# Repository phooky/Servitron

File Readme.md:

Servotron Six
=============

Servotron Six is a six-axis DC servo control board initially developed to support PUMA robot arms and their cousins. It presumes that each servo consists of a DC gearmotor, a quadrature encoder, and optionally an index channel. It uses a BeagleBone A5 or greater to control the system and is designed so that your application can run directly on the BeagleBone.

It has not yet been tested with the new BeagleBone Black.

Hardware
--------

The board is designed to run off a 24V power supply. A switching supply provides 5V to the logic chips and the BeagleBone. Each servo channel is driven by a VNH3SP30 which can provide a peak of ~20A.

The hardware design files are in the "electronics/six_axis_board" directory. The hardware is licenced under the CERN Open Hardware License v1.1.

Software
--------

The software which runs on the BeagleBone is in the "servotron" directory.

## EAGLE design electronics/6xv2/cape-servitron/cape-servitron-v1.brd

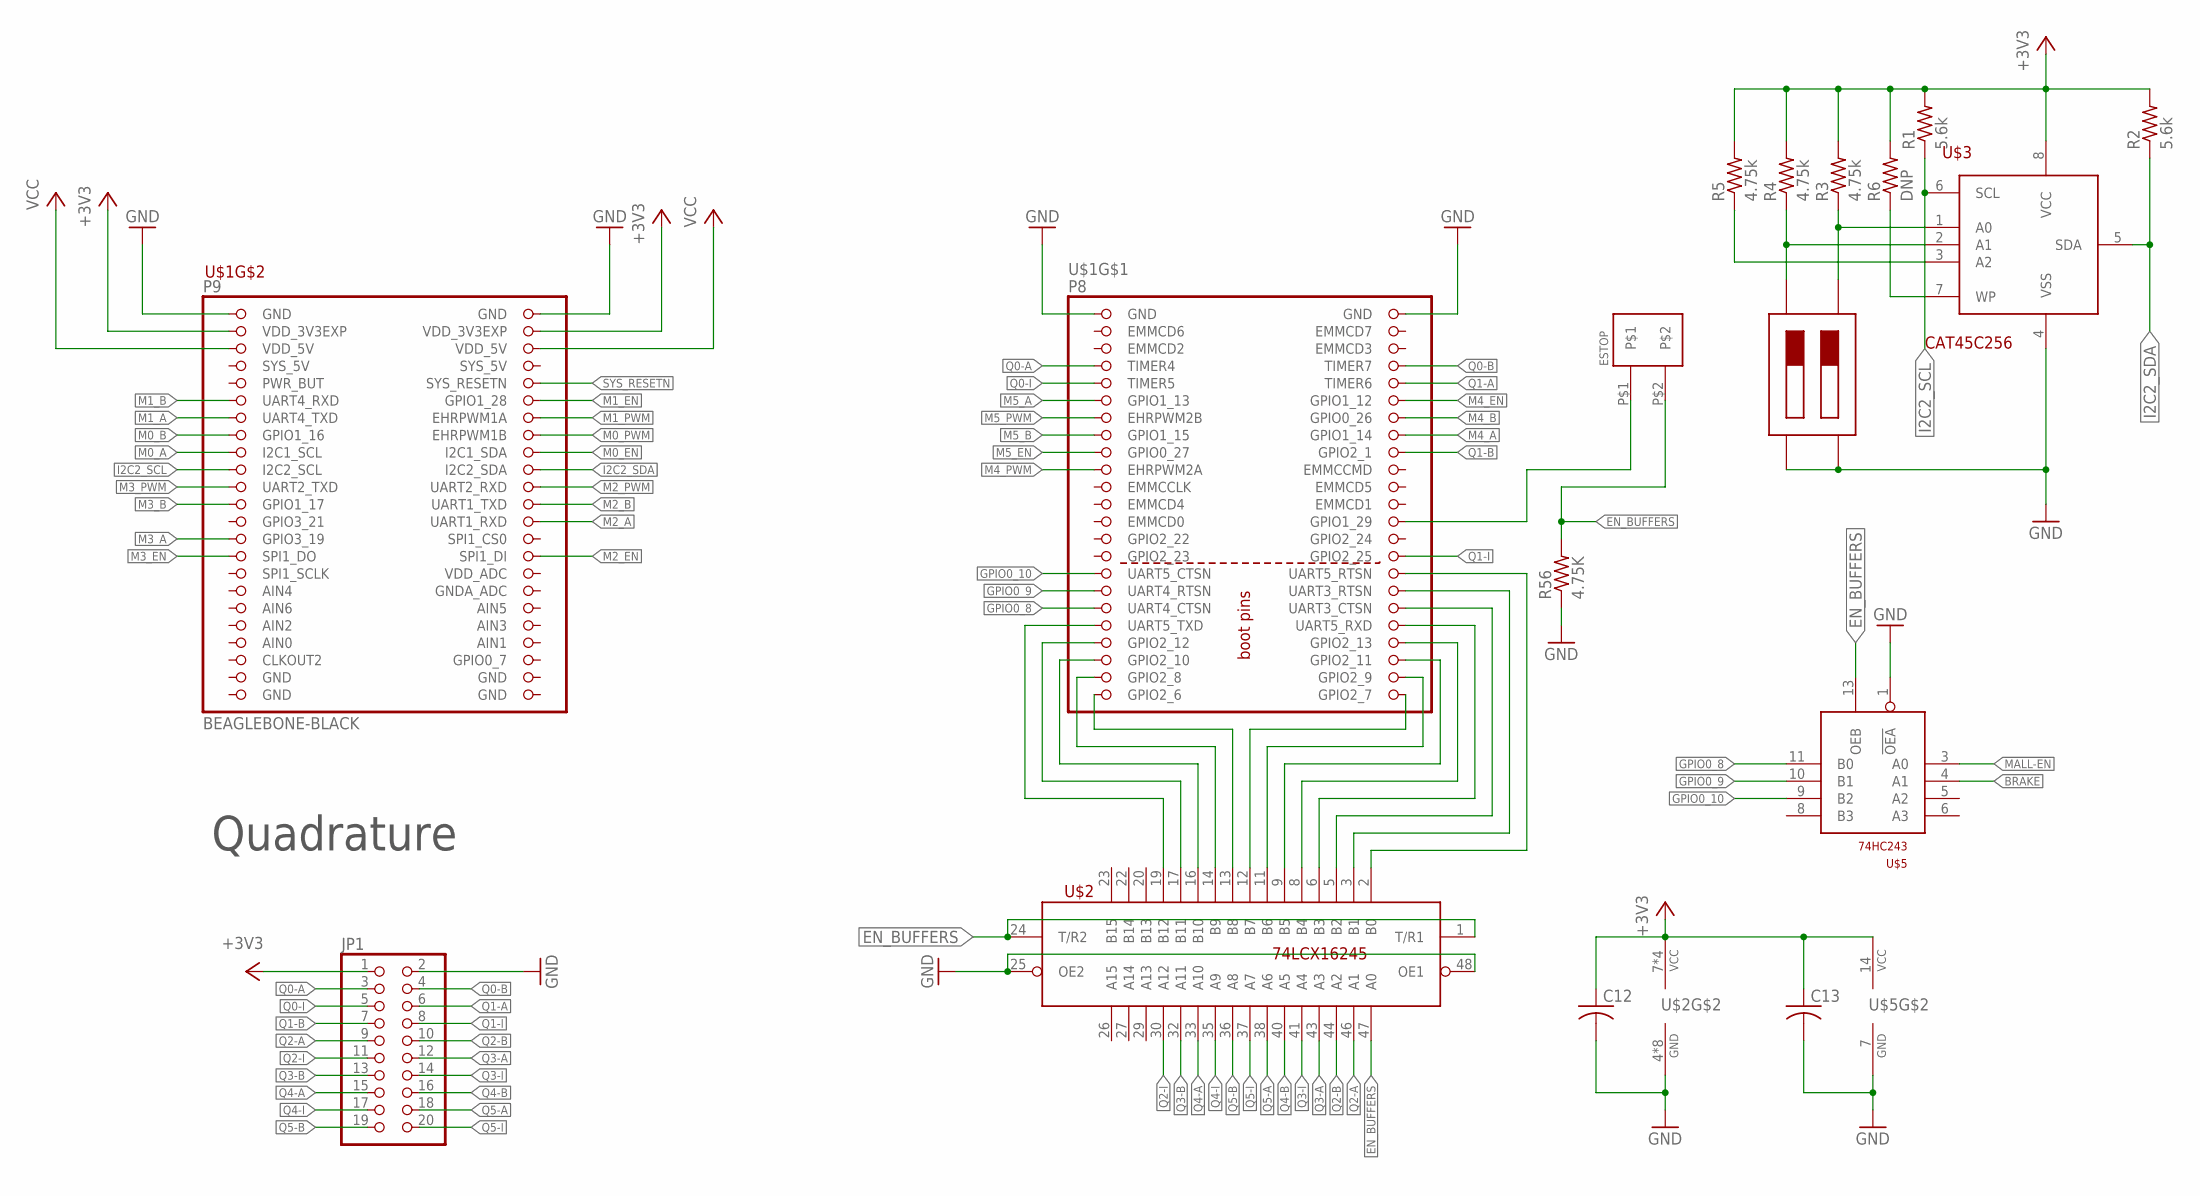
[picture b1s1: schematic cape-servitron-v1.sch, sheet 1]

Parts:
C12, C13: C-USC0805; C0805
ESTOP: PINHEAD-5MM-1X2; 5MM-HEADER-2
JP1: PINHD-2X10; 2X10
R1, R2: 5.6k; R0805
R3, R4, R5: 4.75k; R0805
R6: DNP; R0805
R56: 4.75K; R0805
U$1: BEAGLEBONE-BLACK; BEAGLEBONE_SHIELD
U$2: 74LCX16245; TSSOP-48
U$3: CAT24C2256Y; TSSOP-8
U$4: DIP-SW-2; CT219-2
U$5: 74HC243D; SO14

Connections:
!MALL-EN: U$5.3 (A0); also elsewhere on the board
+3V3: C12.1, C13.1, JP1.1, R1.2, R2.2, R3.2, R4.2, R5.2, R6.2, U$1.49 (VDD_3V3EXP), U$1.50 (VDD_3V3EXP), U$2.7 (VCC), U$2.18 (VCC), U$2.31 (VCC), U$2.42 (VCC), U$3.8 (VCC), U$5.14 (VCC); also elsewhere on the board
BRAKE: U$5.4 (A1); also elsewhere on the board
EN_BUFFERS: ESTOP.P$2, R56.2, U$2.1 (T/R1), U$2.24 (T/R2), U$2.47 (A0), U$5.13 (OEB)
GND: C12.2, C13.2, JP1.2, R56.1, U$1.1 (GND), U$1.2 (GND), U$1.47 (GND), U$1.48 (GND), U$1.89 (GND), U$1.90 (GND), U$1.91 (GND), U$1.92 (GND), U$2.4 (GND), U$2.10 (GND), U$2.15 (GND), U$2.21 (GND), U$2.25 (OE2), U$2.28 (GND), U$2.34 (GND), U$2.39 (GND), U$2.45 (GND), U$2.48 (OE1), U$3.4 (VSS), U$4.1, U$4.2, U$5.1 (!OEA), U$5.7 (GND); also elsewhere on the board
GPIO0_8: U$1.35 (UART4_CTSN), U$5.11 (B0)
GPIO0_9: U$1.33 (UART4_RTSN), U$5.10 (B1)
GPIO0_10: U$1.31 (UART5_CTSN), U$5.9 (B2)
I2C2_SCL: R1.1, U$1.65 (I2C2_SCL), U$3.6 (SCL)
I2C2_SDA: R2.1, U$1.66 (I2C2_SDA), U$3.5 (SDA)
M0_A: U$1.63 (I2C1_SCL); also elsewhere on the board
M0_B: U$1.61 (GPIO1_16); also elsewhere on the board
M0_EN: U$1.64 (I2C1_SDA); also elsewhere on the board
M0_PWM: U$1.62 (EHRPWM1B); also elsewhere on the board
M1_A: U$1.59 (UART4_TXD); also elsewhere on the board
M1_B: U$1.57 (UART4_RXD); also elsewhere on the board
M1_EN: U$1.58 (GPIO1_28); also elsewhere on the board
M1_PWM: U$1.60 (EHRPWM1A); also elsewhere on the board
M2_A: U$1.72 (UART1_RXD); also elsewhere on the board
M2_B: U$1.70 (UART1_TXD); also elsewhere on the board
M2_EN: U$1.76 (SPI1_DI); also elsewhere on the board
M2_PWM: U$1.68 (UART2_RXD); also elsewhere on the board
M3_A: U$1.73 (GPIO3_19); also elsewhere on the board
M3_B: U$1.69 (GPIO1_17); also elsewhere on the board
M3_EN: U$1.75 (SPI1_DO); also elsewhere on the board
M3_PWM: U$1.67 (UART2_TXD); also elsewhere on the board
M4_A: U$1.16 (GPIO1_14); also elsewhere on the board
M4_B: U$1.14 (GPIO0_26); also elsewhere on the board
M4_EN: U$1.12 (GPIO1_12); also elsewhere on the board
M4_PWM: U$1.19 (EHRPWM2A); also elsewhere on the board
M5_A: U$1.11 (GPIO1_13); also elsewhere on the board
M5_B: U$1.15 (GPIO1_15); also elsewhere on the board
M5_EN: U$1.17 (GPIO0_27); also elsewhere on the board
M5_PWM: U$1.13 (EHRPWM2B); also elsewhere on the board
unnamed: U$1.45 (GPIO2_6), U$2.13 (B8)
unnamed: U$1.46 (GPIO2_7), U$2.12 (B7)
unnamed: U$1.43 (GPIO2_8), U$2.14 (B9)
unnamed: U$1.44 (GPIO2_9), U$2.11 (B6)
unnamed: U$1.41 (GPIO2_10), U$2.16 (B10)
unnamed: U$1.42 (GPIO2_11), U$2.9 (B5)
unnamed: U$1.40 (GPIO2_13), U$2.8 (B4)
unnamed: U$1.39 (GPIO2_12), U$2.17 (B11)
unnamed: U$1.37 (UART5_TXD), U$2.19 (B12)
unnamed: U$1.38 (UART5_RXD), U$2.6 (B3)
unnamed: U$1.36 (UART3_CTSN), U$2.5 (B2)
unnamed: U$1.34 (UART3_RTSN), U$2.3 (B1)
unnamed: R3.1, U$3.1 (A0), U$4.4
unnamed: R4.1, U$3.2 (A1), U$4.3
unnamed: R5.1, U$3.3 (A2)
unnamed: R6.1, U$3.7 (WP)
unnamed: U$1.32 (UART5_RTSN), U$2.2 (B0)
unnamed: ESTOP.P$1, U$1.26 (GPIO1_29)
Q0-A: JP1.3, U$1.7 (TIMER4)
Q0-B: JP1.4, U$1.8 (TIMER7)
Q0-I: JP1.5, U$1.9 (TIMER5)
Q1-A: JP1.6, U$1.10 (TIMER6)
Q1-B: JP1.7, U$1.18 (GPIO2_1)
Q1-I: JP1.8, U$1.30 (GPIO2_25)
Q2-A: JP1.9, U$2.46 (A1)
Q2-B: JP1.10, U$2.44 (A2)
Q2-I: JP1.11, U$2.30 (A12)
Q3-A: JP1.12, U$2.43 (A3)
Q3-B: JP1.13, U$2.32 (A11)
Q3-I: JP1.14, U$2.41 (A4)
Q4-A: JP1.15, U$2.33 (A10)
Q4-B: JP1.16, U$2.40 (A5)
Q4-I: JP1.17, U$2.35 (A9)
Q5-A: JP1.18, U$2.38 (A6)
Q5-B: JP1.19, U$2.36 (A8)
Q5-I: JP1.20, U$2.37 (A7)
SYS_RESETN: U$1.56 (SYS_RESETN)
VCC: U$1.51 (VDD_5V), U$1.52 (VDD_5V); also elsewhere on the board

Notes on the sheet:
Quadrature

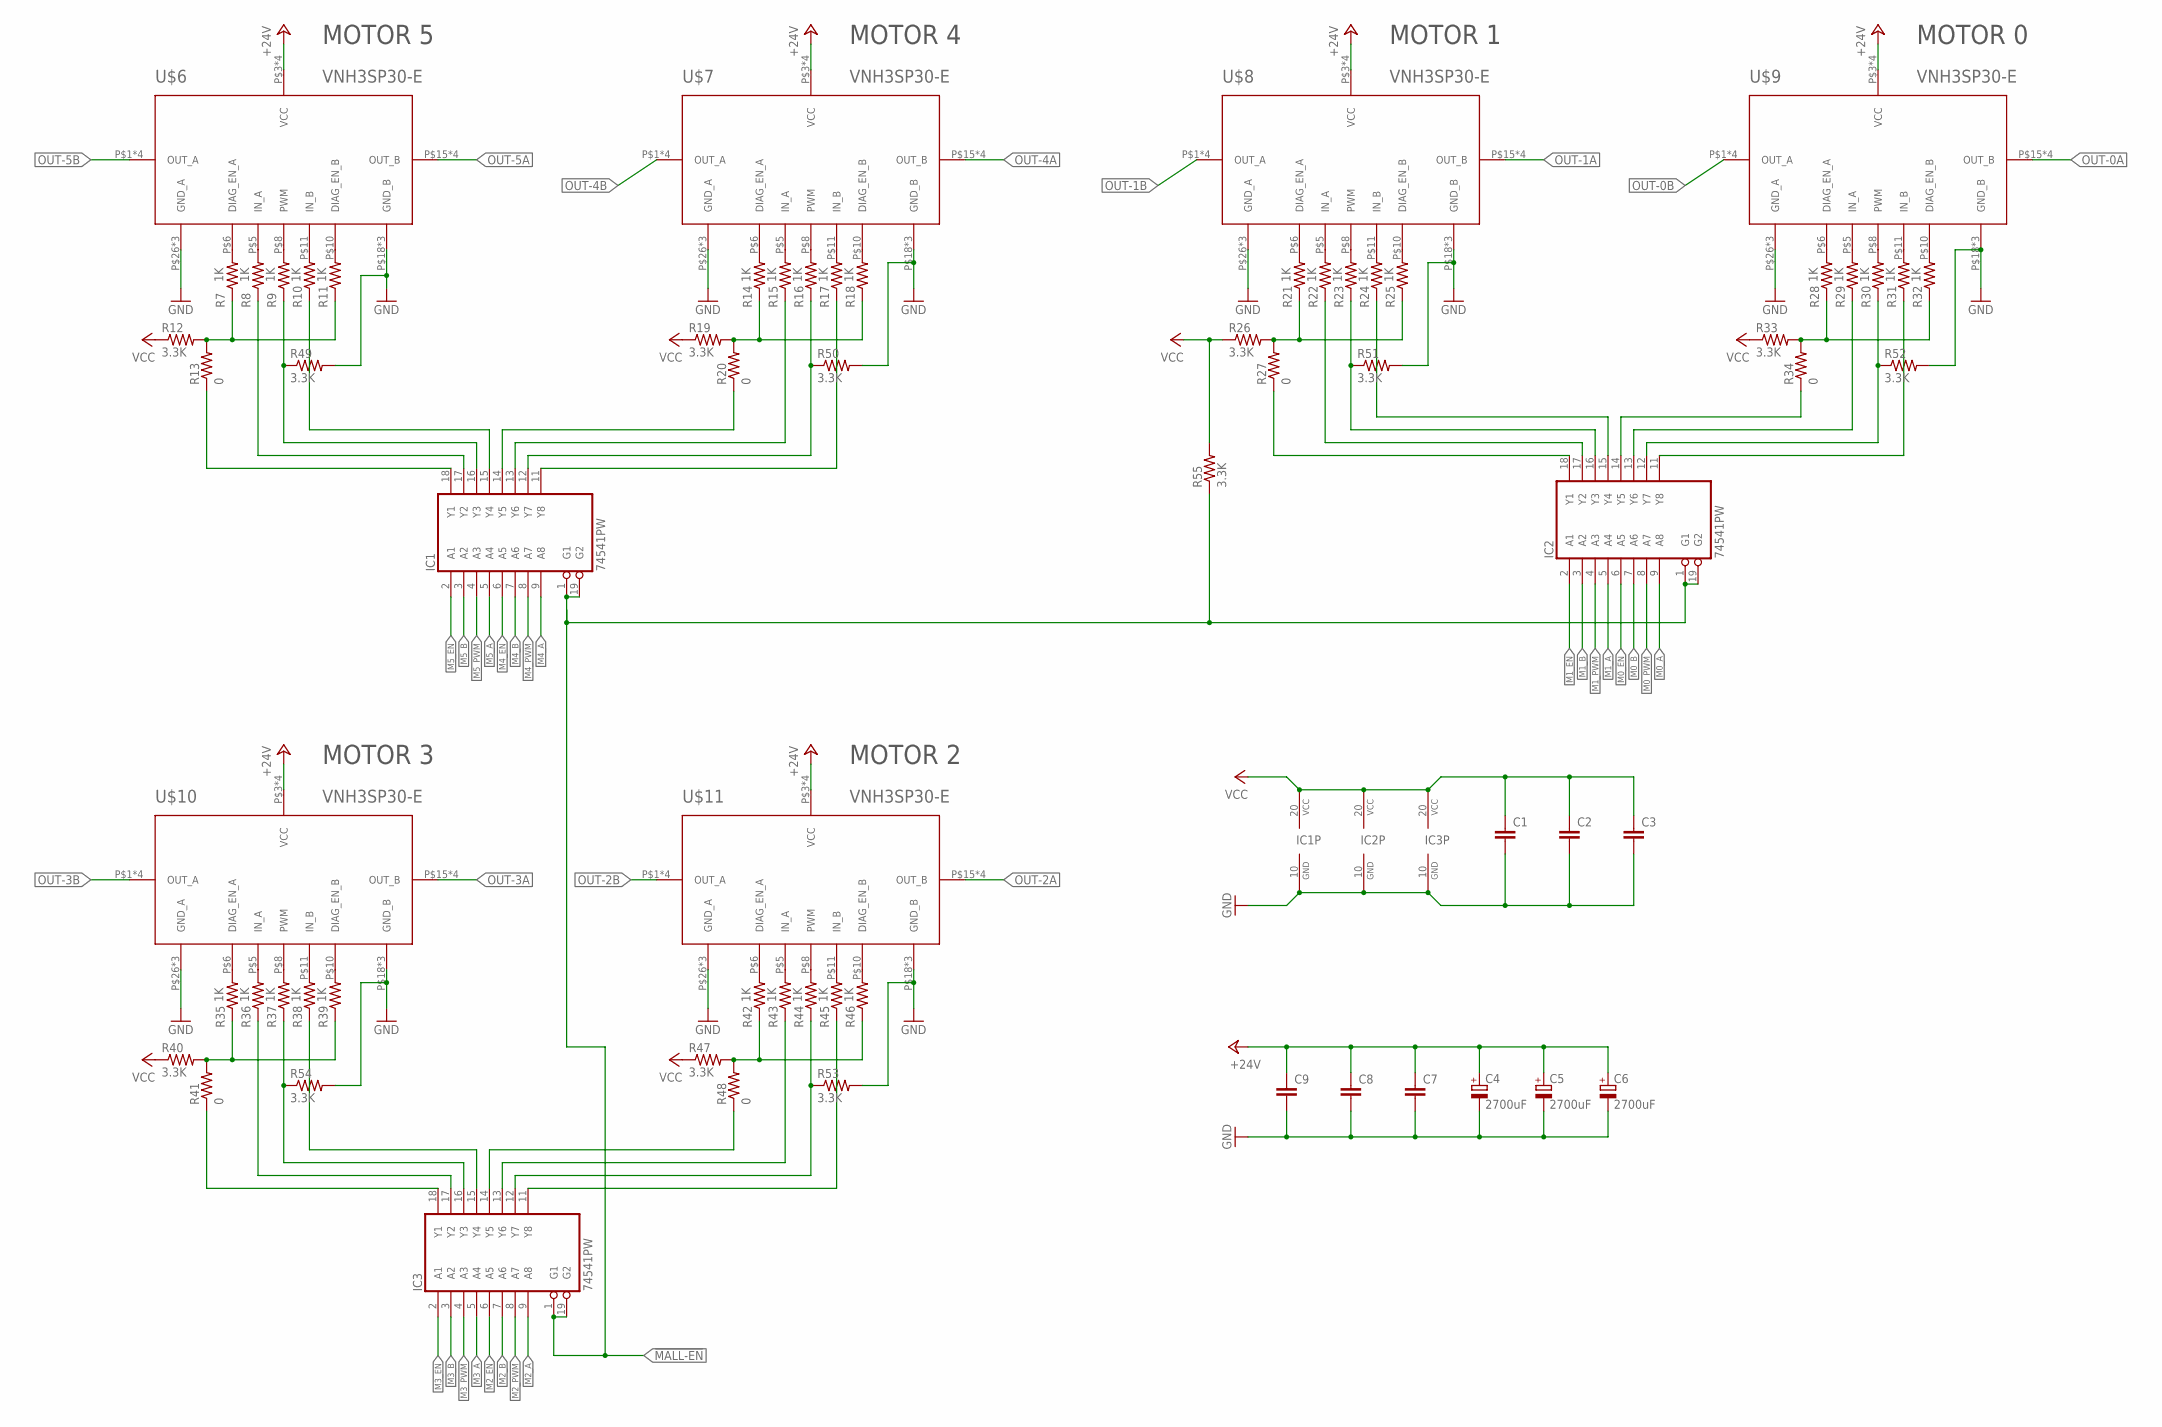
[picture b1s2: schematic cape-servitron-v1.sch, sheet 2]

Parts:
C1, C2, C3, C7, C8, C9: C-EUC1206; C1206
C4, C5, C6: 2700uF; E5-13
IC1, IC2, IC3: 74541PW; TSSOP-20
R7, R8, R9, R10, R11, R14, R15, R16, R17, R18, R21, R22, R23, R24, R25, R28, R29, R30, R31, R32, R35, R36, R37, R38, R39, R42, R43, R44, R45, R46: 1K; R0805
R12, R19, R26, R33, R40, R47, R49, R50, R51, R52, R53, R54, R55: 3.3K; R0805
R13, R20, R27, R34, R41, R48: 0; R0805
U$6, U$7, U$8, U$9, U$10, U$11: VNH3SP30-E; MULTIPOWER-SO-30

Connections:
!MALL-EN: IC1.1 (G1), IC1.19 (G2), IC2.1 (G1), IC2.19 (G2), IC3.1 (G1), IC3.19 (G2), R55.1; also elsewhere on the board
+24V: C4.+, C5.+, C6.+, C7.1, C8.1, C9.1, U$6.P$3 (VCC), U$6.P$13 (VCC), U$6.P$23 (VCC), U$6.T$3 (VCC), U$7.P$3 (VCC), U$7.P$13 (VCC), U$7.P$23 (VCC), U$7.T$3 (VCC), U$8.P$3 (VCC), U$8.P$13 (VCC), U$8.P$23 (VCC), U$8.T$3 (VCC), U$9.P$3 (VCC), U$9.P$13 (VCC), U$9.P$23 (VCC), U$9.T$3 (VCC), U$10.P$3 (VCC), U$10.P$13 (VCC), U$10.P$23 (VCC), U$10.T$3 (VCC), U$11.P$3 (VCC), U$11.P$13 (VCC), U$11.P$23 (VCC), U$11.T$3 (VCC); also elsewhere on the board
GND: C1.2, C2.2, C3.2, C4.-, C5.-, C6.-, C7.2, C8.2, C9.2, IC1.10 (GND), IC2.10 (GND), IC3.10 (GND), R49.2, R50.2, R51.2, R52.2, R53.2, R54.2, U$6.P$18 (GND_B), U$6.P$19 (GND_B), U$6.P$20 (GND_B), U$6.P$26 (GND_A), U$6.P$27 (GND_A), U$6.P$28 (GND_A), U$7.P$18 (GND_B), U$7.P$19 (GND_B), U$7.P$20 (GND_B), U$7.P$26 (GND_A), U$7.P$27 (GND_A), U$7.P$28 (GND_A), U$8.P$18 (GND_B), U$8.P$19 (GND_B), U$8.P$20 (GND_B), U$8.P$26 (GND_A), U$8.P$27 (GND_A), U$8.P$28 (GND_A), U$9.P$18 (GND_B), U$9.P$19 (GND_B), U$9.P$20 (GND_B), U$9.P$26 (GND_A), U$9.P$27 (GND_A), U$9.P$28 (GND_A), U$10.P$18 (GND_B), U$10.P$19 (GND_B), U$10.P$20 (GND_B), U$10.P$26 (GND_A), U$10.P$27 (GND_A), U$10.P$28 (GND_A), U$11.P$18 (GND_B), U$11.P$19 (GND_B), U$11.P$20 (GND_B), U$11.P$26 (GND_A), U$11.P$27 (GND_A), U$11.P$28 (GND_A); also elsewhere on the board
M0_A: IC2.9 (A8); also elsewhere on the board
M0_B: IC2.7 (A6); also elsewhere on the board
M0_EN: IC2.6 (A5); also elsewhere on the board
M0_PWM: IC2.8 (A7); also elsewhere on the board
M1_A: IC2.5 (A4); also elsewhere on the board
M1_B: IC2.3 (A2); also elsewhere on the board
M1_EN: IC2.2 (A1); also elsewhere on the board
M1_PWM: IC2.4 (A3); also elsewhere on the board
M2_A: IC3.9 (A8); also elsewhere on the board
M2_B: IC3.7 (A6); also elsewhere on the board
M2_EN: IC3.6 (A5); also elsewhere on the board
M2_PWM: IC3.8 (A7); also elsewhere on the board
M3_A: IC3.5 (A4); also elsewhere on the board
M3_B: IC3.3 (A2); also elsewhere on the board
M3_EN: IC3.2 (A1); also elsewhere on the board
M3_PWM: IC3.4 (A3); also elsewhere on the board
M4_A: IC1.9 (A8); also elsewhere on the board
M4_B: IC1.7 (A6); also elsewhere on the board
M4_EN: IC1.6 (A5); also elsewhere on the board
M4_PWM: IC1.8 (A7); also elsewhere on the board
M5_A: IC1.5 (A4); also elsewhere on the board
M5_B: IC1.3 (A2); also elsewhere on the board
M5_EN: IC1.2 (A1); also elsewhere on the board
M5_PWM: IC1.4 (A3); also elsewhere on the board
unnamed: R7.2, U$6.P$6 (DIAG_EN_A)
unnamed: R7.1, R11.1, R12.2, R13.2
unnamed: IC1.18 (Y1), R13.1
unnamed: IC1.17 (Y2), R8.1
unnamed: IC1.16 (Y3), R9.1, R49.1
unnamed: IC1.15 (Y4), R10.1
unnamed: R8.2, U$6.P$5 (IN_A)
unnamed: R9.2, U$6.P$8 (PWM)
unnamed: R10.2, U$6.P$11 (IN_B)
unnamed: R11.2, U$6.P$10 (DIAG_EN_B)
unnamed: R14.2, U$7.P$6 (DIAG_EN_A)
unnamed: R14.1, R18.1, R19.2, R20.2
unnamed: IC1.11 (Y8), R17.1
unnamed: IC1.12 (Y7), R16.1, R50.1
unnamed: IC1.13 (Y6), R15.1
unnamed: IC1.14 (Y5), R20.1
unnamed: R21.2, U$8.P$6 (DIAG_EN_A)
unnamed: R21.1, R25.1, R26.2, R27.2
unnamed: IC2.18 (Y1), R27.1
unnamed: IC2.17 (Y2), R22.1
unnamed: IC2.16 (Y3), R23.1, R51.1
unnamed: IC2.15 (Y4), R24.1
unnamed: R22.2, U$8.P$5 (IN_A)
unnamed: R23.2, U$8.P$8 (PWM)
unnamed: R24.2, U$8.P$11 (IN_B)
unnamed: R25.2, U$8.P$10 (DIAG_EN_B)
unnamed: R28.2, U$9.P$6 (DIAG_EN_A)
unnamed: R28.1, R32.1, R33.2, R34.2
unnamed: IC2.11 (Y8), R31.1
unnamed: IC2.12 (Y7), R30.1, R52.1
unnamed: IC2.13 (Y6), R29.1
unnamed: IC2.14 (Y5), R34.1
unnamed: R35.2, U$10.P$6 (DIAG_EN_A)
unnamed: R35.1, R39.1, R40.2, R41.2
unnamed: IC3.18 (Y1), R41.1
unnamed: IC3.11 (Y8), R45.1
unnamed: IC3.17 (Y2), R36.1
unnamed: IC3.16 (Y3), R37.1, R54.1
unnamed: R36.2, U$10.P$5 (IN_A)
unnamed: R37.2, U$10.P$8 (PWM)
unnamed: R38.2, U$10.P$11 (IN_B)
unnamed: R39.2, U$10.P$10 (DIAG_EN_B)
unnamed: R42.2, U$11.P$6 (DIAG_EN_A)
unnamed: R42.1, R46.1, R47.2, R48.2
unnamed: IC3.15 (Y4), R38.1
unnamed: IC3.12 (Y7), R44.1, R53.1
unnamed: IC3.13 (Y6), R43.1
unnamed: IC3.14 (Y5), R48.1
unnamed: R45.2, U$11.P$11 (IN_B)
unnamed: R44.2, U$11.P$8 (PWM)
unnamed: R43.2, U$11.P$5 (IN_A)
unnamed: R46.2, U$11.P$10 (DIAG_EN_B)
unnamed: R18.2, U$7.P$10 (DIAG_EN_B)
unnamed: R17.2, U$7.P$11 (IN_B)
unnamed: R16.2, U$7.P$8 (PWM)
unnamed: R15.2, U$7.P$5 (IN_A)
unnamed: R32.2, U$9.P$10 (DIAG_EN_B)
unnamed: R31.2, U$9.P$11 (IN_B)
unnamed: R30.2, U$9.P$8 (PWM)
unnamed: R29.2, U$9.P$5 (IN_A)
OUT-0A: U$9.P$15 (OUT_B), U$9.P$16 (OUT_B), U$9.P$21 (OUT_B), U$9.T$2 (OUT_B); also elsewhere on the board
OUT-0B: U$9.P$1 (OUT_A), U$9.P$25 (OUT_A), U$9.P$30 (OUT_A), U$9.T$1 (OUT_A); also elsewhere on the board
OUT-1A: U$8.P$15 (OUT_B), U$8.P$16 (OUT_B), U$8.P$21 (OUT_B), U$8.T$2 (OUT_B); also elsewhere on the board
OUT-1B: U$8.P$1 (OUT_A), U$8.P$25 (OUT_A), U$8.P$30 (OUT_A), U$8.T$1 (OUT_A); also elsewhere on the board
OUT-2A: U$11.P$15 (OUT_B), U$11.P$16 (OUT_B), U$11.P$21 (OUT_B), U$11.T$2 (OUT_B); also elsewhere on the board
OUT-2B: U$11.P$1 (OUT_A), U$11.P$25 (OUT_A), U$11.P$30 (OUT_A), U$11.T$1 (OUT_A); also elsewhere on the board
OUT-3A: U$10.P$15 (OUT_B), U$10.P$16 (OUT_B), U$10.P$21 (OUT_B), U$10.T$2 (OUT_B); also elsewhere on the board
OUT-3B: U$10.P$1 (OUT_A), U$10.P$25 (OUT_A), U$10.P$30 (OUT_A), U$10.T$1 (OUT_A); also elsewhere on the board
OUT-4A: U$7.P$15 (OUT_B), U$7.P$16 (OUT_B), U$7.P$21 (OUT_B), U$7.T$2 (OUT_B); also elsewhere on the board
OUT-4B: U$7.P$1 (OUT_A), U$7.P$25 (OUT_A), U$7.P$30 (OUT_A), U$7.T$1 (OUT_A); also elsewhere on the board
OUT-5A: U$6.P$15 (OUT_B), U$6.P$16 (OUT_B), U$6.P$21 (OUT_B), U$6.T$2 (OUT_B); also elsewhere on the board
OUT-5B: U$6.P$1 (OUT_A), U$6.P$25 (OUT_A), U$6.P$30 (OUT_A), U$6.T$1 (OUT_A); also elsewhere on the board
VCC: C1.1, C2.1, C3.1, IC1.20 (VCC), IC2.20 (VCC), IC3.20 (VCC), R12.1, R19.1, R26.1, R33.1, R40.1, R47.1, R55.2; also elsewhere on the board

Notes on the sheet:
MOTOR 5
MOTOR 4
MOTOR 1
MOTOR 0
MOTOR 3
MOTOR 2

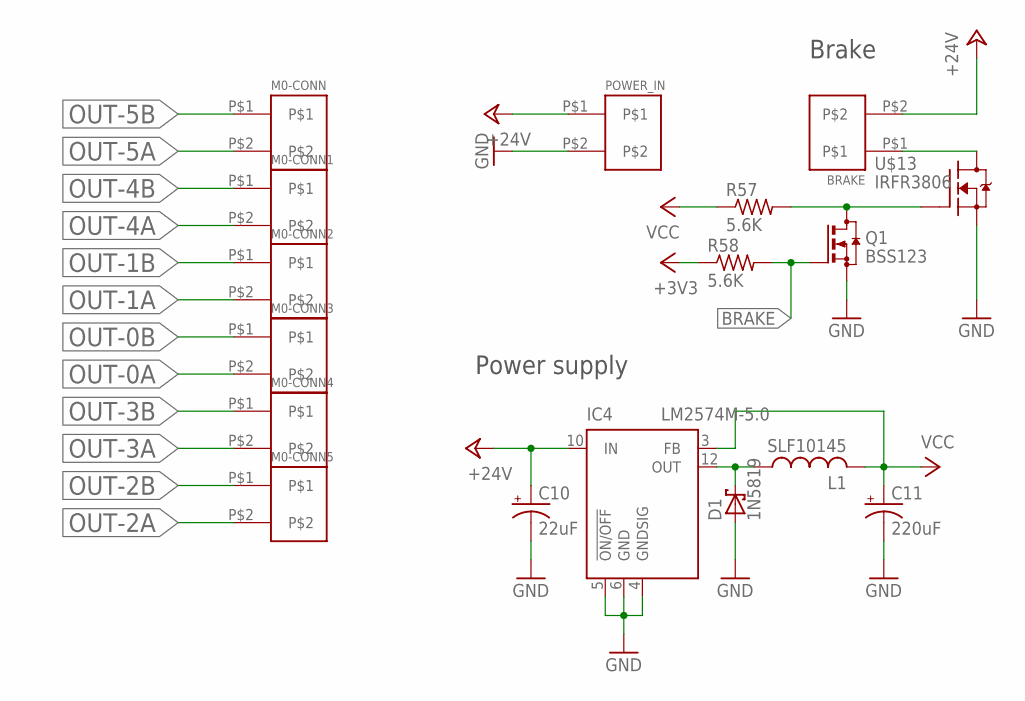
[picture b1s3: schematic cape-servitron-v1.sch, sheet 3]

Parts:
BRAKE: PINHEAD-5MM-1X2; 5MM-HEADER-2
C10: 22uF; SANYO-OSCON_SMD_E7
C11: 220uF; SANYO-OSCON_SMD_F8
D1: 1N5819; SOD-123
IC4: LM2574M-5.0; SO14W
L1: SLF10145; SMD10145
M0-CONN, M0-CONN1, M0-CONN2, M0-CONN3, M0-CONN4, M0-CONN5: PINHEAD-5MM-1X2; 5MM-HEADER-2
POWER_IN: PINHEAD-5MM-1X2; 5MM-HEADER-2
Q1: BSS123; SOT23
R57, R58: 5.6K; R0805
U$13: IRFR3806; TO252

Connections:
+3V3: R58.1; also elsewhere on the board
+24V: BRAKE.P$2, C10.+, IC4.10 (IN), POWER_IN.P$1; also elsewhere on the board
BRAKE: Q1.1 (G), R58.2; also elsewhere on the board
GND: C10.-, C11.-, D1.A, IC4.4 (GNDSIG), IC4.5 (!ON/OFF), IC4.6 (GND), POWER_IN.P$2, Q1.2 (S), U$13.2 (S); also elsewhere on the board
unnamed: D1.C, IC4.12 (OUT), L1.P$1 (1)
unnamed: BRAKE.P$1, U$13.3 (D)
unnamed: Q1.3 (D), R57.2, U$13.1 (G)
OUT-0A: M0-CONN3.P$2; also elsewhere on the board
OUT-0B: M0-CONN3.P$1; also elsewhere on the board
OUT-1A: M0-CONN2.P$2; also elsewhere on the board
OUT-1B: M0-CONN2.P$1; also elsewhere on the board
OUT-2A: M0-CONN5.P$2; also elsewhere on the board
OUT-2B: M0-CONN5.P$1; also elsewhere on the board
OUT-3A: M0-CONN4.P$2; also elsewhere on the board
OUT-3B: M0-CONN4.P$1; also elsewhere on the board
OUT-4A: M0-CONN1.P$2; also elsewhere on the board
OUT-4B: M0-CONN1.P$1; also elsewhere on the board
OUT-5A: M0-CONN.P$2; also elsewhere on the board
OUT-5B: M0-CONN.P$1; also elsewhere on the board
VCC: C11.+, IC4.3 (FB), L1.P$2 (2), R57.1; also elsewhere on the board

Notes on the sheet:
Power supply
Brake

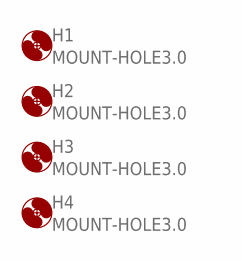
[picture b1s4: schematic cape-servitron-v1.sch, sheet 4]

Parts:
H1, H2, H3, H4: MOUNT-HOLE3.0; 3,0

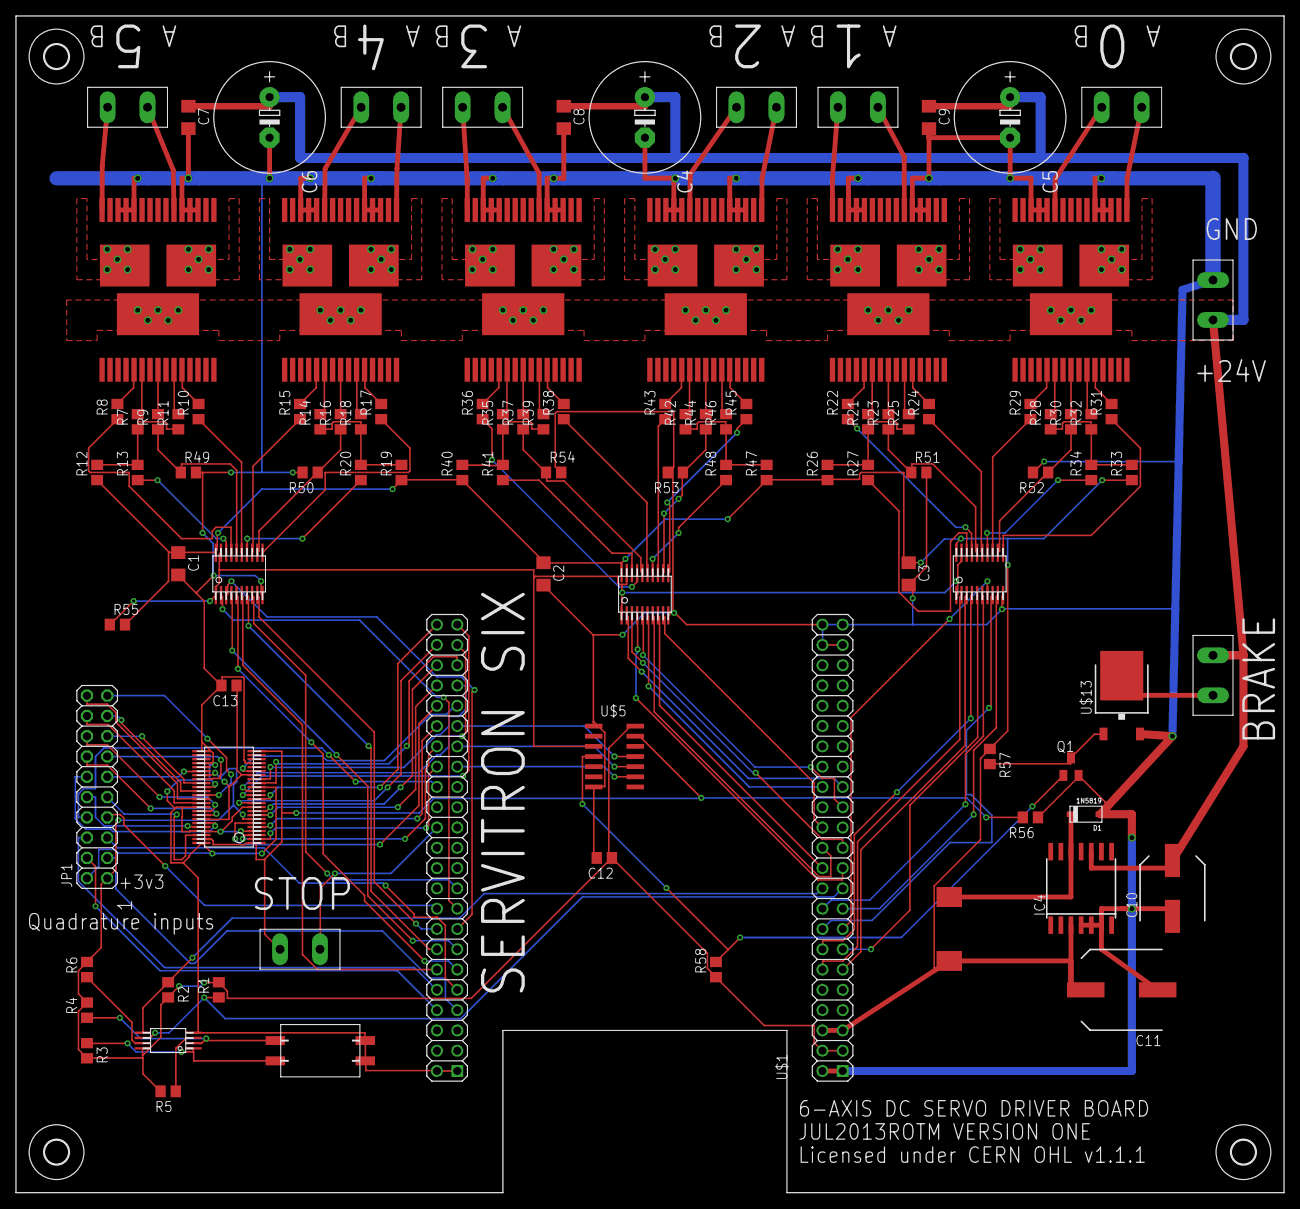
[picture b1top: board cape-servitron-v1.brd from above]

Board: 2 copper layers, 158.8 x 147.3 mm, 104 parts (0 on the bottom side), 147 nets.

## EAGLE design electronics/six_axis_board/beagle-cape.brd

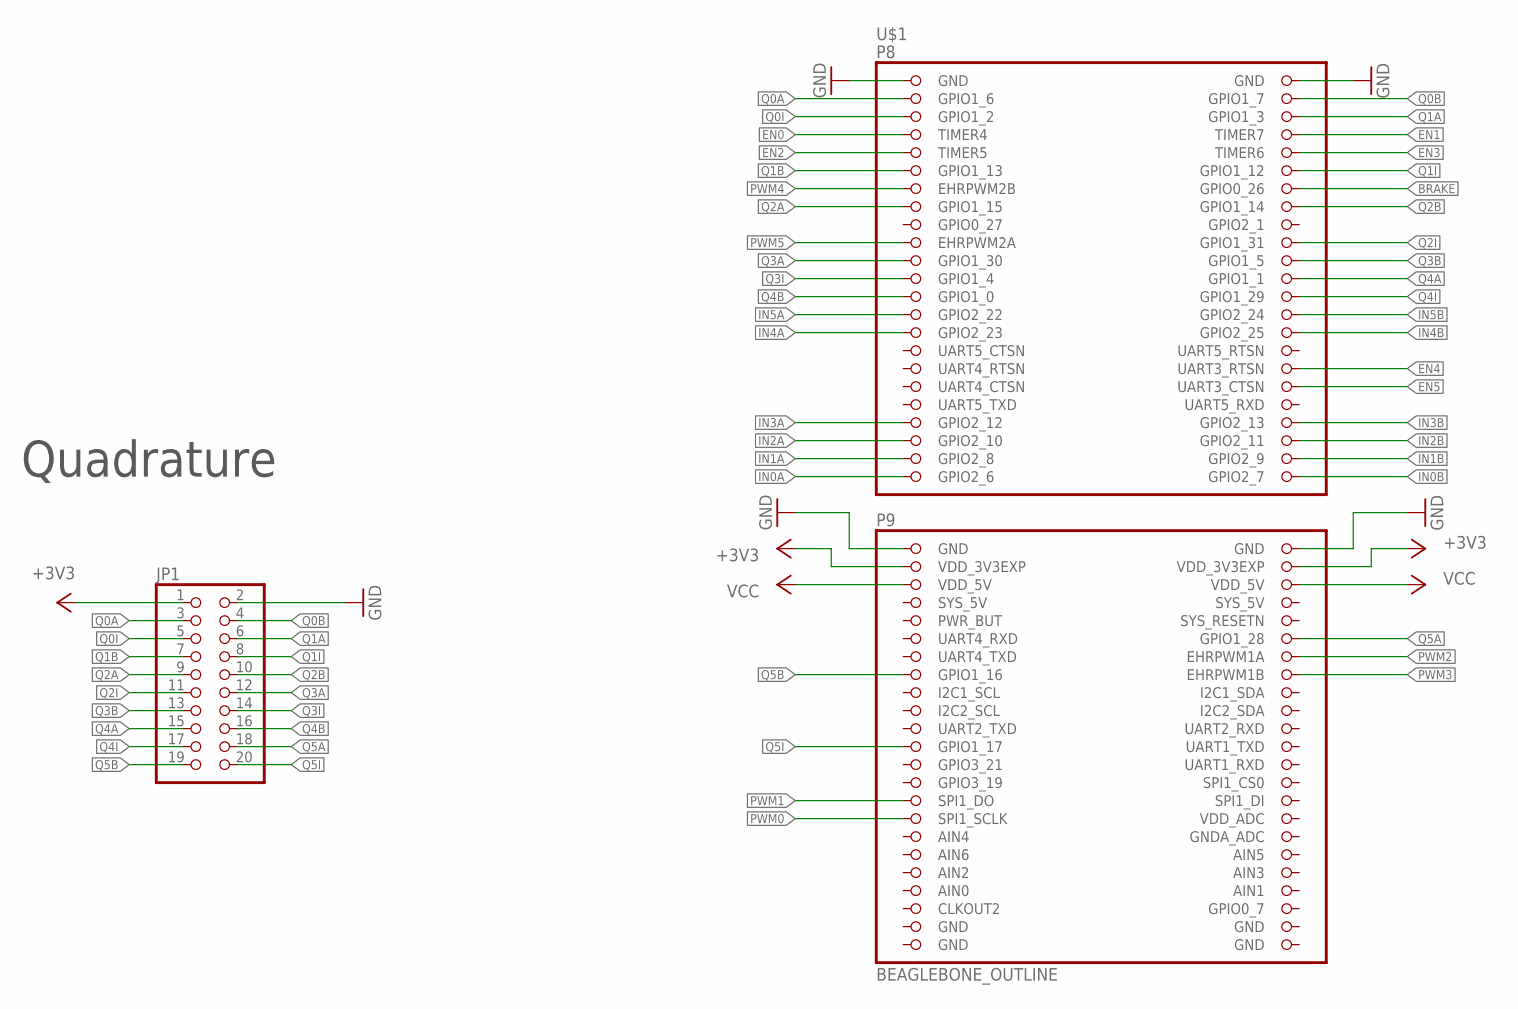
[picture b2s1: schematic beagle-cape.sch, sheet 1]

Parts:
JP1: PINHD-2X10; 2X10
U$1: BEAGLEBONE_OUTLINE; BEAGLEBONE_SHIELD

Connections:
+3V3: JP1.1, U$1.49 (VDD_3V3EXP), U$1.50 (VDD_3V3EXP); also elsewhere on the board
BRAKE: U$1.14 (GPIO0_26); also elsewhere on the board
EN0: U$1.7 (TIMER4); also elsewhere on the board
EN1: U$1.8 (TIMER7); also elsewhere on the board
EN2: U$1.9 (TIMER5); also elsewhere on the board
EN3: U$1.10 (TIMER6); also elsewhere on the board
EN4: U$1.34 (UART3_RTSN); also elsewhere on the board
EN5: U$1.36 (UART3_CTSN); also elsewhere on the board
GND: JP1.2, U$1.1 (GND), U$1.2 (GND), U$1.47 (GND), U$1.48 (GND), U$1.89 (GND), U$1.90 (GND), U$1.91 (GND), U$1.92 (GND); also elsewhere on the board
IN0A: U$1.45 (GPIO2_6); also elsewhere on the board
IN0B: U$1.46 (GPIO2_7); also elsewhere on the board
IN1A: U$1.43 (GPIO2_8); also elsewhere on the board
IN1B: U$1.44 (GPIO2_9); also elsewhere on the board
IN2A: U$1.41 (GPIO2_10); also elsewhere on the board
IN2B: U$1.42 (GPIO2_11); also elsewhere on the board
IN3A: U$1.39 (GPIO2_12); also elsewhere on the board
IN3B: U$1.40 (GPIO2_13); also elsewhere on the board
IN4A: U$1.29 (GPIO2_23); also elsewhere on the board
IN4B: U$1.30 (GPIO2_25); also elsewhere on the board
IN5A: U$1.27 (GPIO2_22); also elsewhere on the board
IN5B: U$1.28 (GPIO2_24); also elsewhere on the board
PWM0: U$1.77 (SPI1_SCLK); also elsewhere on the board
PWM1: U$1.75 (SPI1_DO); also elsewhere on the board
PWM2: U$1.60 (EHRPWM1A); also elsewhere on the board
PWM3: U$1.62 (EHRPWM1B); also elsewhere on the board
PWM4: U$1.13 (EHRPWM2B); also elsewhere on the board
PWM5: U$1.19 (EHRPWM2A); also elsewhere on the board
Q0A: JP1.3, U$1.3 (GPIO1_6)
Q0B: JP1.4, U$1.4 (GPIO1_7)
Q0I: JP1.5, U$1.5 (GPIO1_2)
Q1A: JP1.6, U$1.6 (GPIO1_3)
Q1B: JP1.7, U$1.11 (GPIO1_13)
Q1I: JP1.8, U$1.12 (GPIO1_12)
Q2A: JP1.9, U$1.15 (GPIO1_15)
Q2B: JP1.10, U$1.16 (GPIO1_14)
Q2I: JP1.11, U$1.20 (GPIO1_31)
Q3A: JP1.12, U$1.21 (GPIO1_30)
Q3B: JP1.13, U$1.22 (GPIO1_5)
Q3I: JP1.14, U$1.23 (GPIO1_4)
Q4A: JP1.15, U$1.24 (GPIO1_1)
Q4B: JP1.16, U$1.25 (GPIO1_0)
Q4I: JP1.17, U$1.26 (GPIO1_29)
Q5A: JP1.18, U$1.58 (GPIO1_28)
Q5B: JP1.19, U$1.61 (GPIO1_16)
Q5I: JP1.20, U$1.69 (GPIO1_17)
VCC: U$1.51 (VDD_5V), U$1.52 (VDD_5V); also elsewhere on the board

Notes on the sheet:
Quadrature

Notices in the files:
electronics/6xv2/cape-servitron/cape-servitron-v1.brd:
Licensed under CERN OHL v1.1.1
